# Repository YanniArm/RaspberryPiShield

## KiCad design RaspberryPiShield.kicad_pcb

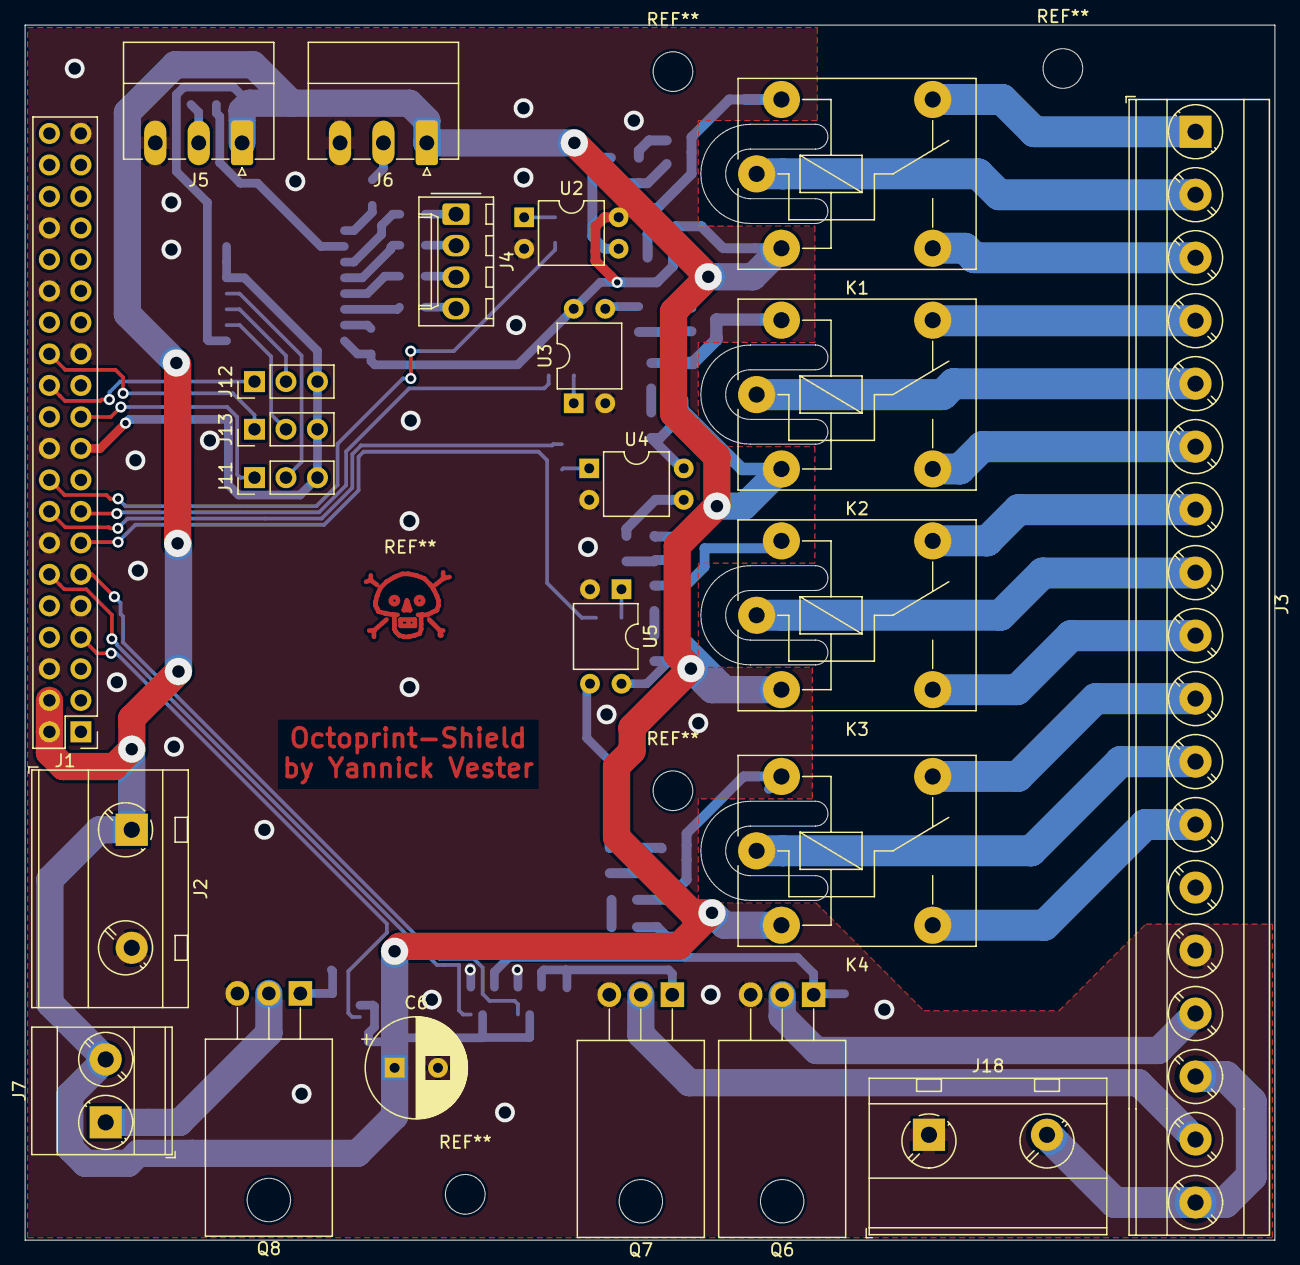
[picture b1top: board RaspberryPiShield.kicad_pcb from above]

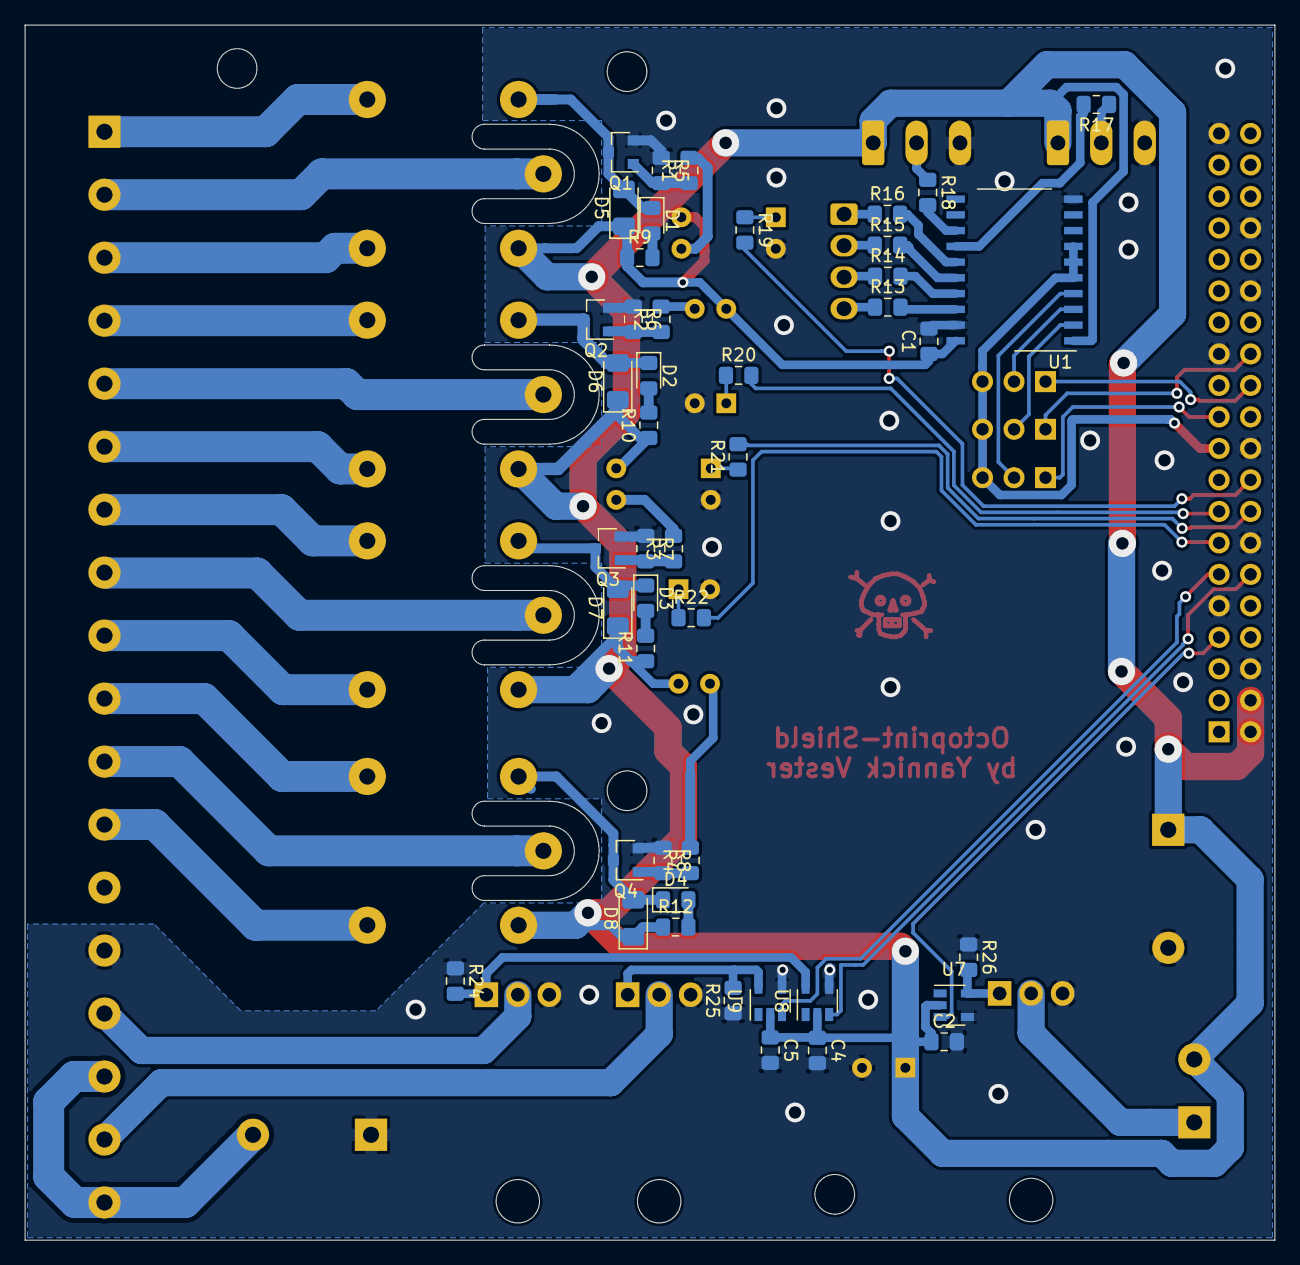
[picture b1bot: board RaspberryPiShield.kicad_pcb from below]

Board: 4 copper layers, 100.8 x 98.0 mm, 68 parts (45 on the bottom side), 70 nets.

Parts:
C1, C2, C4, C5: C; C_0805_2012Metric_Pad1.15x1.40mm_HandSolder
C6: CP; CP_Radial_D8.0mm_P3.50mm
D1, D2, D3, D4: LED; LED_0805_2012Metric_Pad1.15x1.40mm_HandSolder
D5, D6, D7, D8: D; D_1206_3216Metric_Pad1.42x1.75mm_HandSolder
J1: Raspberry_Pi_2_3; PinHeader_2x20_P2.54mm_Vertical
J2, J18: Conn_01x02; TerminalBlock_MetzConnect_Type703_RT10N02HGLU_1x02_P9.52mm_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
J3: Conn_01x18; TerminalBlock_Phoenix_MKDS-3-16-5.08_1x16_P5.08mm_Horizontal
J4: Conn_01x04; Molex_KK-254_AE-6410-04A_1x04_P2.54mm_Vertical
J5, J6: Conn_01x03; PhoenixContact_MC_1,5_3-G-3.5_1x03_P3.50mm_Horizontal
J7: Conn_01x02; TerminalBlock_Phoenix_MKDS-3-2-5.08_1x02_P5.08mm_Horizontal
J11, J12, J13: Conn_01x03; PinHeader_1x03_P2.54mm_Vertical
K1, K2, K3, K4: FINDER-40.11; Relay_SPDT_Finder_36.11
Q1, Q2, Q3, Q4: BSS123; SOT-23
Q6, Q7, Q8: IRLZ44N; TO-220-3_Horizontal_TabDown
R1, R2, R3, R4, R9, R10, R11, R12, R19, R20, R21, R22: 1k; R_0805_2012Metric_Pad1.15x1.40mm_HandSolder
R5, R6, R7, R8, R24, R25, R26: 22k; R_0805_2012Metric_Pad1.15x1.40mm_HandSolder
R13, R14, R15, R16, R17, R18: R; R_0805_2012Metric_Pad1.15x1.40mm_HandSolder
U1: 74HC245; SO-20_12.8x7.5mm_P1.27mm
U2, U3, U4, U5: PC817; DIP-4_W7.62mm
U7, U8, U9: MCP1416; SOT-23-5

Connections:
+3V3: J1.1, J1.17
+5V: C1.1, C2.1, C4.1, C5.1, C6.1, D5.1, D6.1, D7.1, D8.1, J1.2, J1.4, J2.1, J5.1, J6.1, J7.2, K1.A1, K2.A1, K3.A1, K4.A1, R9.1, R10.1, R11.1, R12.1, U1.1, U1.20, U2.4, U3.4, U4.4, U5.4, U7.2, U8.2, U9.2
+24V: J3.16, J3.18, J18.2
/relay/out1: J1.12, U8.3
/relay/out2: J1.11, U9.3
/relay/out3: J1.7, U7.3
/relay/relay1: J1.18, R19.2
/relay/relay2: J1.15, R20.2
/relay/relay3: J1.16, R21.2
/relay/relay4: J1.13, R22.2
GND: C1.2, C2.2, C4.2, C5.2, C6.2, J1.6, J1.9, J1.14, J1.20, J1.25, J1.30, J1.34, J1.39, J2.2, J3.14, J5.3, J6.3, J18.1, Q1.2, Q2.2, Q3.2, Q4.2, Q6.3, Q7.3, Q8.3, R5.1, R6.1, R7.1, R8.1, R24.1, R25.1, R26.1, U1.10, U1.19, U2.2, U3.2, U4.2, U5.2, U7.4, U8.4, U9.4
unnamed: D1.1, D5.2, K1.A2, Q1.3
unnamed: D1.2, R9.2
unnamed: D2.1, D6.2, K2.A2, Q2.3
unnamed: D2.2, R10.2
unnamed: D3.1, D7.2, K3.A2, Q3.3
unnamed: D3.2, R11.2
unnamed: D4.1, D8.2, K4.A2, Q4.3
unnamed: D4.2, R12.2
unnamed: J1.3, U1.8
unnamed: J1.5, U1.9
unnamed: J1.19, J11.3, J12.3, J13.3, U1.5, U1.6, U1.7
unnamed: J1.21, J11.1
unnamed: J1.24, J12.1
unnamed: J1.26, J13.1
unnamed: J3.1, K1.12
unnamed: J3.2, K1.11
unnamed: J3.3, K1.14
unnamed: J3.4, K2.12
unnamed: J3.5, K2.11
unnamed: J3.6, K2.14
unnamed: J3.7, K3.12
unnamed: J3.8, K3.11
unnamed: J3.9, K3.14
unnamed: J3.10, K4.12
unnamed: J3.11, K4.11
unnamed: J3.12, K4.14
unnamed: J3.15, Q6.2
unnamed: J3.17, Q7.2
unnamed: J4.1, R16.1
unnamed: J4.2, R15.1
unnamed: J4.3, R14.1
unnamed: J4.4, R13.1
unnamed: J5.2, R17.1
unnamed: J6.2, R18.1
unnamed: J7.1, Q8.2
unnamed: J11.2, U1.4
unnamed: J12.2, U1.3
unnamed: J13.2, U1.2
unnamed: Q1.1, R1.1, R5.2
unnamed: Q2.1, R2.1, R6.2
unnamed: Q3.1, R3.1, R7.2
unnamed: Q4.1, R4.1, R8.2
unnamed: Q6.1, R24.2, U8.5
unnamed: Q7.1, R25.2, U9.5
unnamed: Q8.1, R26.2, U7.5
unnamed: R1.2, U2.3
unnamed: R2.2, U3.3
unnamed: R3.2, U4.3
unnamed: R4.2, U5.3
unnamed: R13.2, U1.18
unnamed: R14.2, U1.17
unnamed: R15.2, U1.16
unnamed: R16.2, U1.15
unnamed: R17.2, U1.14
unnamed: R18.2, U1.13
unnamed: R19.1, U2.1
unnamed: R20.1, U3.1
unnamed: R21.1, U4.1
unnamed: R22.1, U5.1
